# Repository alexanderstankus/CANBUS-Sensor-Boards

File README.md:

# CANBUS-Sensor-Boards
Schematic + Layout for CANBUS Protocol, IMU, Wheel Speed, and Suspension following FSAE regulation
# Overview
Prototype node boards for CAN Bus communication featuring an IMU, Wheel Speed sensors, and Suspension sensors. 
# Features
* STM32 (MCU)
* CAN Transceiver MCP2551
* Multiple Buck Converters per board (24v to 5v) and (5v to 3.3v)
# Technical Specifications
* 2 Layer Boards
* 24v Max Input

# Schematic and Layout Examples

Schematic for IMU + STM32

Layout for IMU + STM32

#
The other 2 Schematics and Layouts (wheel speed sensor and suspension sensors) can be found in the exports folder within the repo.

Designed in KiCad by Alexander Stankus

GitHub: @alexanderstankus

Email: alexstankus99@gmail.com

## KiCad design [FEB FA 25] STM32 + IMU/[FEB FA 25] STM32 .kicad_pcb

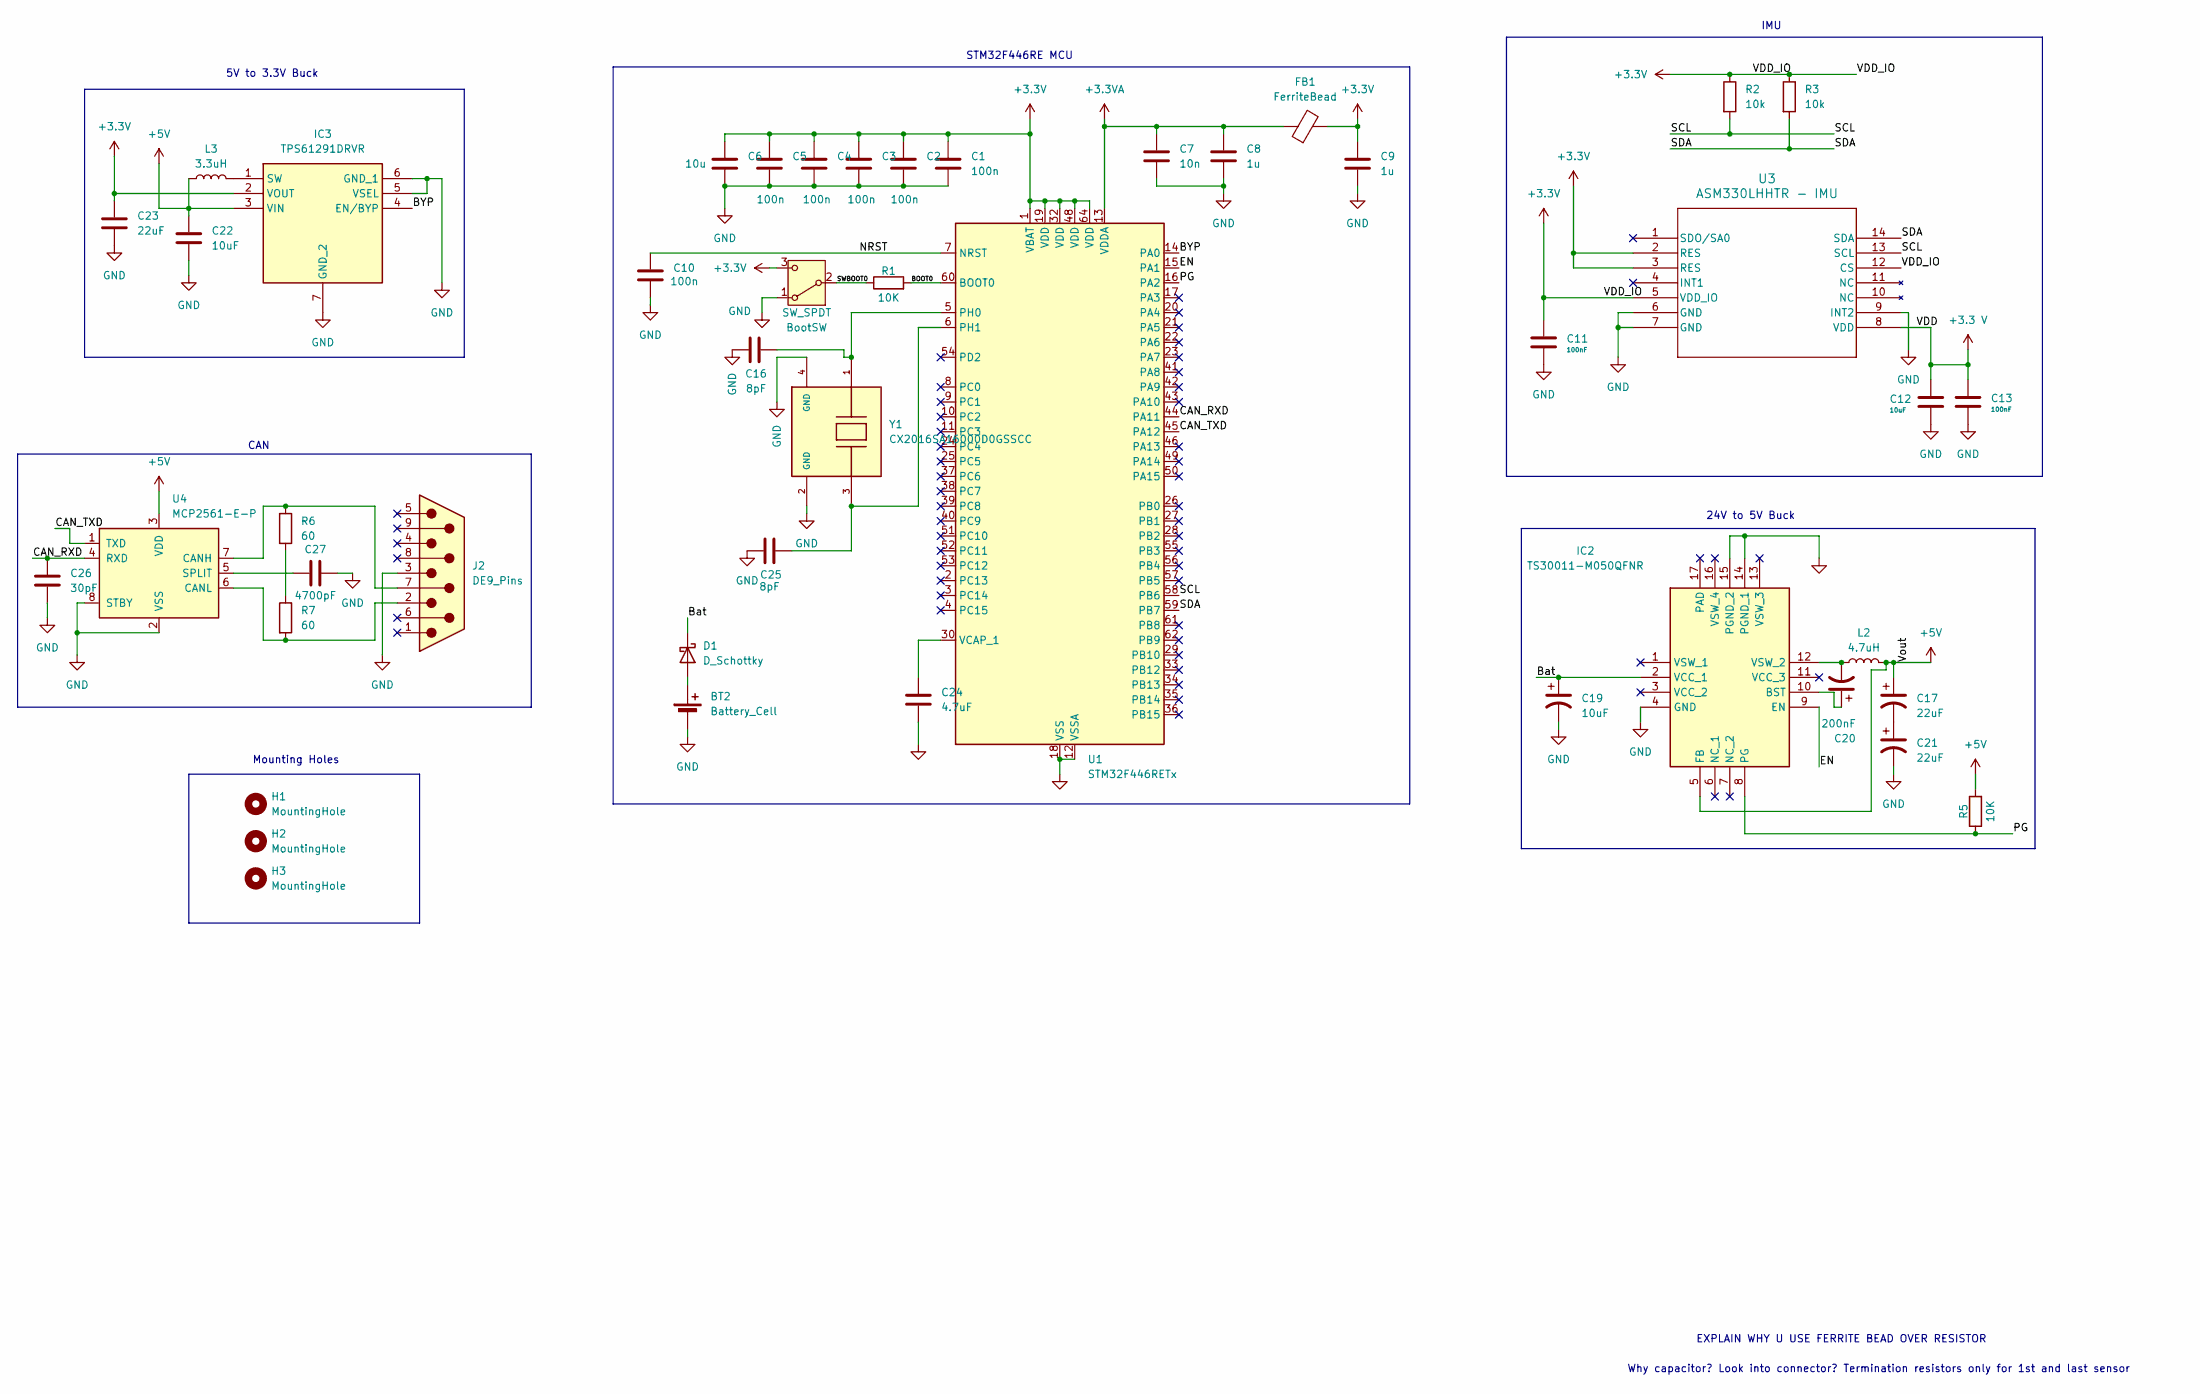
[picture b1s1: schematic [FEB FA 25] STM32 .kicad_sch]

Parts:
BT2: Battery_Cell; 691137710002
BootSW: SW_SPDT; SW_SPDT_CK_JS102011SAQN
C1, C2, C3, C4, C5, C10: 100n; C_0201_0603Metric
C6: 10u; C_1206_3216Metric
C7: 10n; C_0201_0603Metric
C8, C9: 1u; C_0201_0603Metric
C11, C13: 100nF; C_0201_0603Metric
C12, C19, C22: 10uF; C_1206_3216Metric
C16, C25: 8pF; C_0201_0603Metric
C17, C21, C23: 22uF; C_0603_1608Metric
C20: 200nF; C_0603_1608Metric
C24: 4.7uF; C_0201_0603Metric
C26: 30pF; C_0402_1005Metric
C27: 4700pF; C_0603_1608Metric
D1: D_Schottky; D_SMC
FB1: FerriteBead; Crystal_SMD_0603-4Pin_6.0x3.5mm
H1, H2, H3: MountingHole; MountingHole_2.2mm_M2
IC2: TS30011-M050QFNR; Mouser Part Number 947-TS30011-M050QFNR
IC3: TPS61291DRVR; Mouser Part Number 595-TPS61291DRVR
J2: DE9_Pins; DSUB-9_Pins_EdgeMount_P2.77mm
L2: 4.7uH; L_0603_1608Metric
L3: 3.3uH; L_1210_3225Metric
R1, R5: 10K; R_0201_0603Metric
R2, R3: 10k; R_0201_0603Metric
R6, R7: 60; R_1206_3216Metric
U1: STM32F446RETx; LQFP-64_10x10mm_P0.5mm
U3: ASM330LHHTR - IMU
U4: MCP2561-E-P; DIP-8_W7.62mm
Y1: CX2016SA16000D0GSSCC; OSCCC200X160X50N

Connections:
+3.3 V: C12.1, C13.2, U3.8 (VDD)
+3.3V: BootSW.3 (C), C1.1, C2.1, C3.1, C4.1, C5.1, C6.1, C9.1, C11.1, C23.1, FB1.2, IC3.2 (VOUT), R2.1, R3.1, U1.1 (VBAT), U1.19 (VDD), U1.32 (VDD), U1.48 (VDD), U1.64 (VDD), U3.2 (RES), U3.3 (RES), U3.5 (VDD_IO), U3.12 (CS); also elsewhere on the board
+3.3VA: C7.1, C8.1, FB1.1, U1.13 (VDDA)
+5V: C17.1, C22.1, IC2.5 (FB), IC3.3 (VIN), L2.2, L3.1, R5.2, U4.3 (VDD)
/BOOT0: R1.2, U1.60 (BOOT0)
/BYP: IC3.4 (EN/BYP), U1.14 (PA0)
/Bat: C19.1, D1.1 (K), IC2.2 (VCC_1)
/CAN_RXD: C26.2, U1.44 (PA11), U4.4 (RXD)
/CAN_TXD: U1.45 (PA12), U4.1 (TXD)
/EN: IC2.9 (EN), U1.15 (PA1)
/NRST: C10.1, U1.7 (NRST)
/PG: IC2.8 (PG), R5.1, U1.16 (PA2)
/SCL: R2.2, U1.58 (PB6), U3.13 (SCL)
/SDA: R3.2, U1.59 (PB7), U3.14 (SDA)
/SWBOOT0: BootSW.2 (B), R1.1; also elsewhere on the board
GND: BT2.2 (-), BootSW.1 (A), C1.2, C2.2, C3.2, C4.2, C5.2, C6.2, C7.2, C8.2, C9.2, C10.2, C11.2, C12.2, C13.1, C16.1, C19.2, C21.2, C22.2, C23.2, C24.2, C25.1, C26.1, C27.1, IC2.4 (GND), IC2.14 (PGND_1), IC2.15 (PGND_2), IC3.5 (VSEL), IC3.6 (GND_1), IC3.7 (GND_2), J2.3, U1.12 (VSSA), U1.18 (VSS), U1.31 (VSS), U1.47 (VSS), U1.63 (VSS), U3.6 (GND), U3.7 (GND), U3.9 (INT2), U4.2 (VSS), U4.8 (STBY), Y1.2 (GND), Y1.4 (GND); also elsewhere on the board
unnamed: BT2.1 (+), D1.2 (A)
unnamed: C17.2, C21.1
unnamed: C20.1, IC2.10 (BST)
unnamed: C20.2, IC2.12 (VSW_2), L2.1
unnamed: IC3.1 (SW), L3.2
unnamed: R6.2, R7.1
unnamed: C16.2, U1.5 (PH0), Y1.1
unnamed: C25.2, U1.6 (PH1), Y1.3
unnamed: C24.1, U1.30 (VCAP_1)
unnamed: J2.7, R6.1, U4.7 (CANH)
unnamed: J2.2, R7.2, U4.6 (CANL)
unnamed: C27.2, U4.5 (SPLIT)

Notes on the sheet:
EXPLAIN WHY U USE FERRITE BEAD OVER RESISTOR
Why capacitor? Look into connector? Termination resistors only for 1st and last sensor
Mounting Holes
CAN
STM32F446RE MCU
24V to 5V Buck
IMU
5V to 3.3V Buck

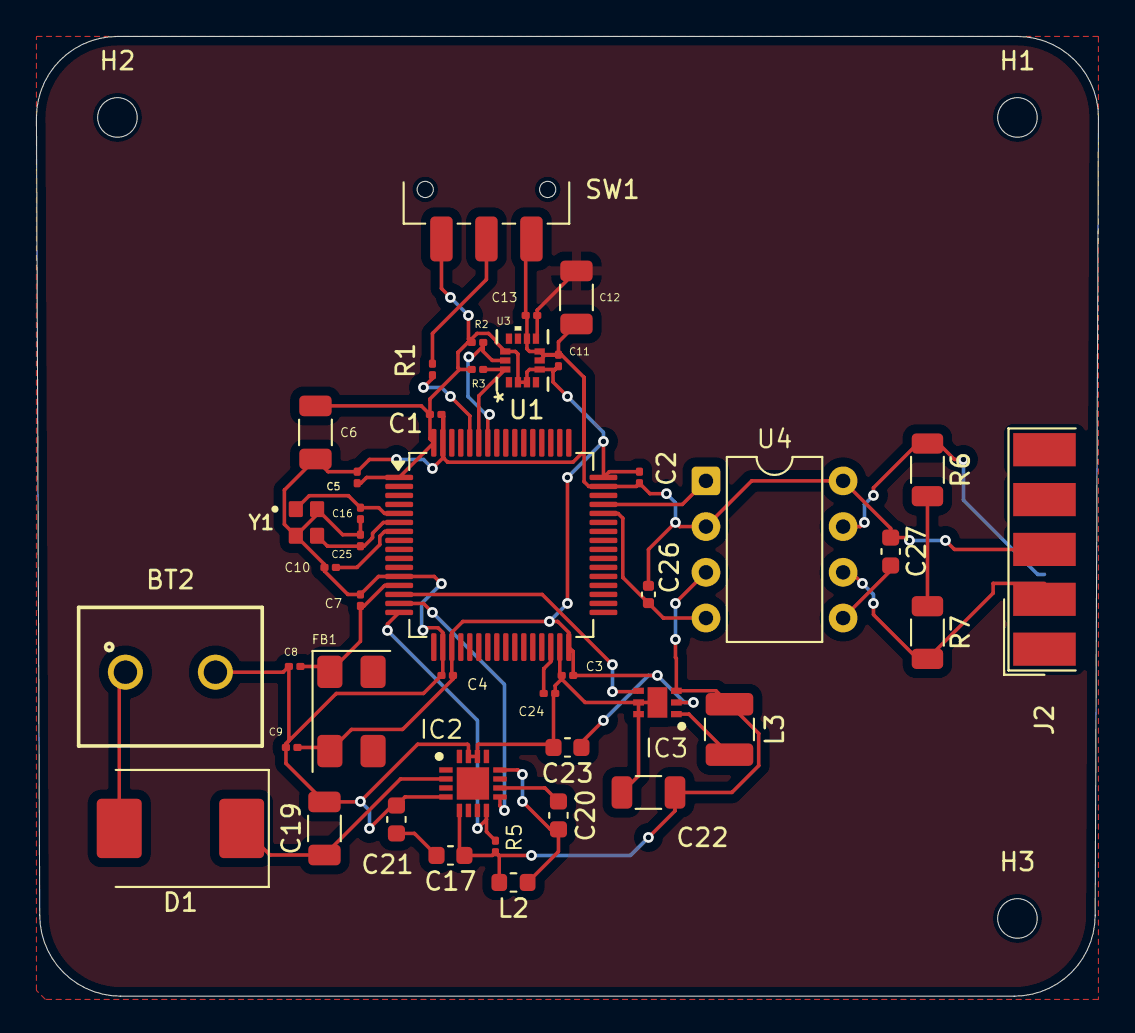
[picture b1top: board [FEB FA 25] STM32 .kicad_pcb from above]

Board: 2 copper layers, 59.0 x 53.3 mm, 46 parts (0 on the bottom side), 28 nets.

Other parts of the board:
SW1: BootSW; SW_SPDT_CK_JS102011SAQN

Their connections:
+3.3V: SW1.3 (C); also elsewhere on the board
/SWBOOT0: SW1.2 (B); also elsewhere on the board
GND: SW1.1 (A); also elsewhere on the board

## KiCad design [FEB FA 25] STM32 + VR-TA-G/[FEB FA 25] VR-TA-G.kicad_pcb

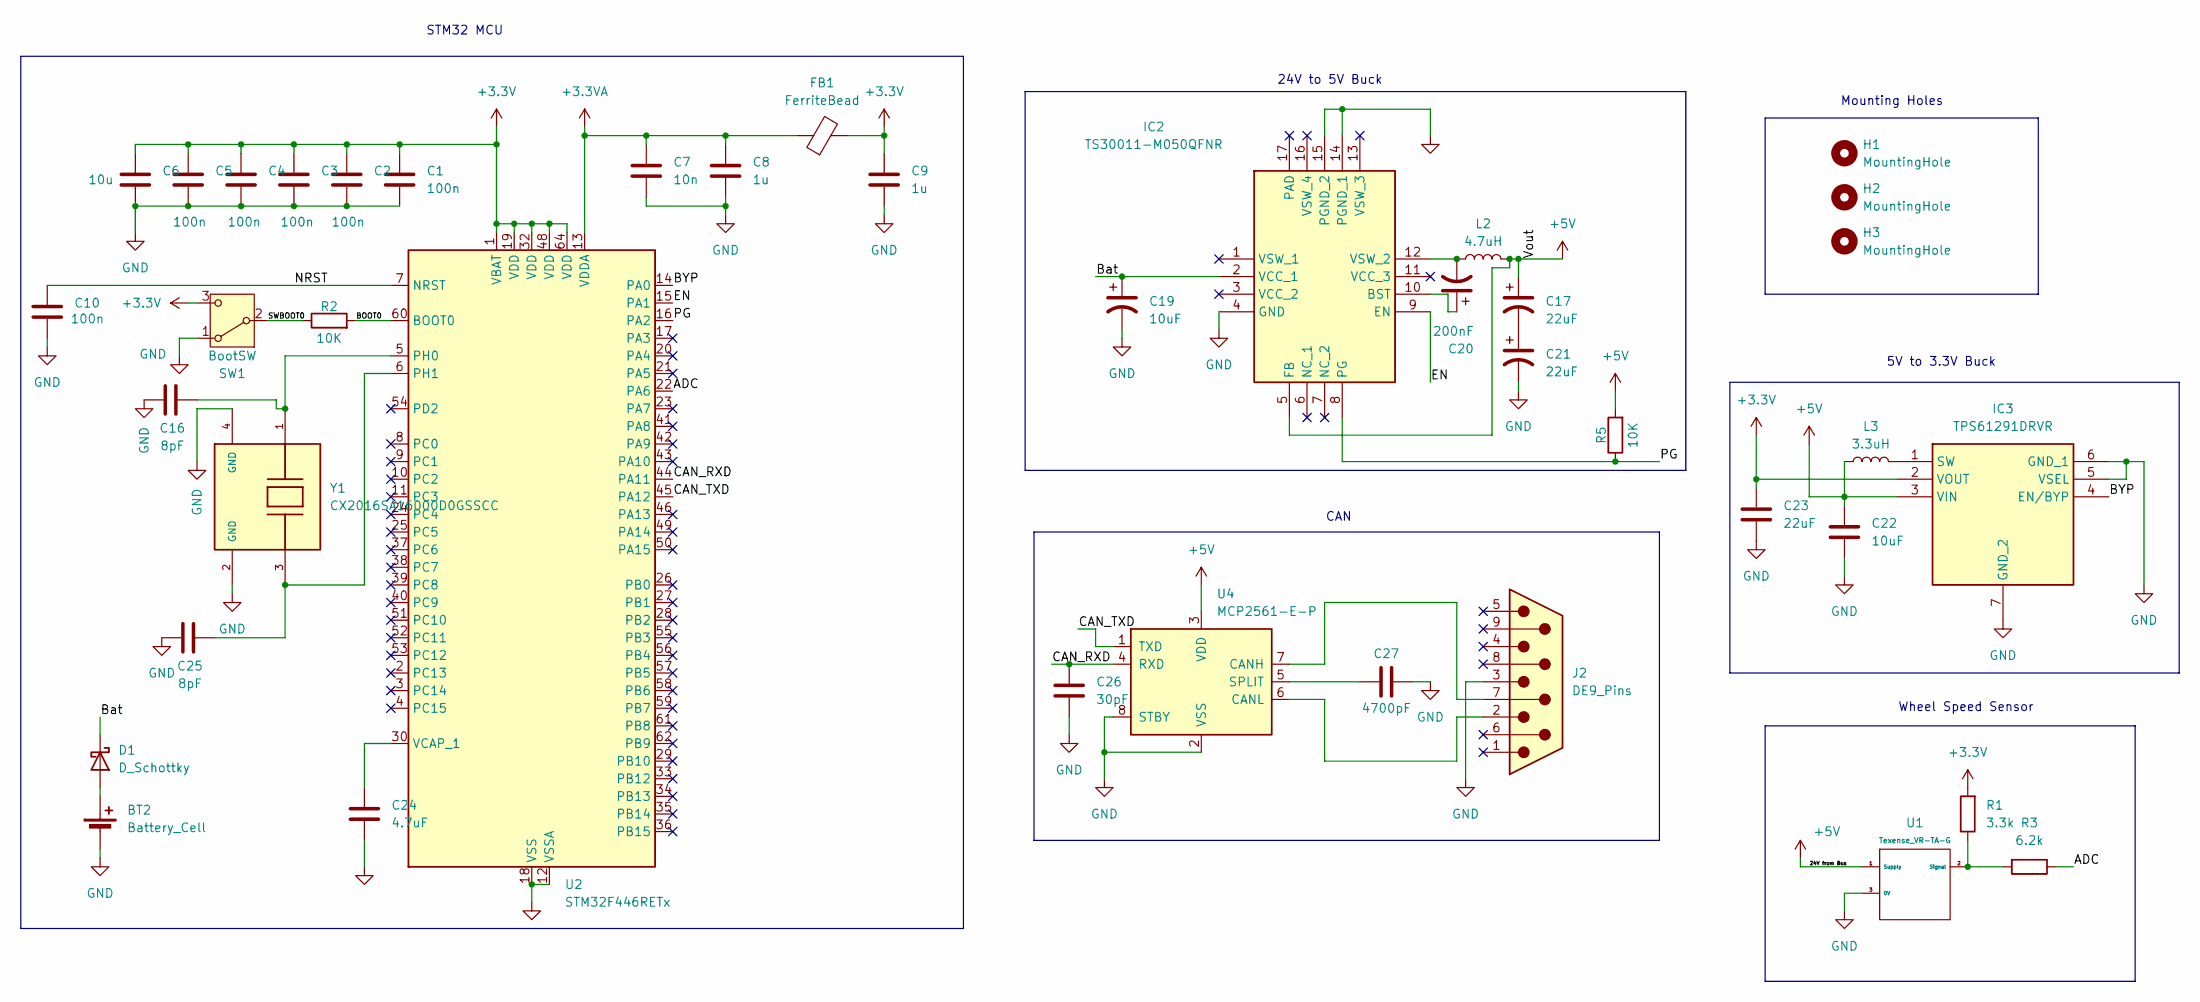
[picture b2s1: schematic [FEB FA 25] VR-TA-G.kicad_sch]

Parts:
BT2: Battery_Cell; 691137710002
C1, C2, C3, C4, C5, C10: 100n; C_0201_0603Metric
C6: 10u; C_1206_3216Metric
C7: 10n; C_0201_0603Metric
C8, C9: 1u; C_0201_0603Metric
C16, C25: 8pF; C_0201_0603Metric
C17, C21, C23: 22uF; C_0603_1608Metric
C19, C22: 10uF; C_1206_3216Metric
C20: 200nF; C_0603_1608Metric
C24: 4.7uF; C_0201_0603Metric
C26: 30pF; C_0402_1005Metric
C27: 4700pF; C_0603_1608Metric
D1: D_Schottky; D_SMC
FB1: FerriteBead; Crystal_SMD_0603-4Pin_6.0x3.5mm
H1, H2, H3: MountingHole; MountingHole_2.2mm_M2
IC2: TS30011-M050QFNR; Mouser Part Number 947-TS30011-M050QFNR
IC3: TPS61291DRVR; Mouser Part Number 595-TPS61291DRVR
J2: DE9_Pins; DSUB-9_Pins_EdgeMount_P2.77mm
L2: 4.7uH; L_0603_1608Metric
L3: 3.3uH; L_1210_3225Metric
R1: 3.3k; R_0201_0603Metric
R2, R5: 10K; R_0201_0603Metric
R3: 6.2k; R_0201_0603Metric
SW1: BootSW; SW_SPDT_CK_JS102011SAQN
U1: Texense_VR-TA-G; CONN_1988817
U2: STM32F446RETx; LQFP-64_10x10mm_P0.5mm
U4: MCP2561-E-P; DIP-8_W7.62mm
Y1: CX2016SA16000D0GSSCC; OSCCC200X160X50N

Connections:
+3.3V: C1.1, C2.1, C3.1, C4.1, C5.1, C6.1, C9.1, C23.1, FB1.2, IC3.2 (VOUT), R1.2, SW1.3 (C), U2.1 (VBAT), U2.19 (VDD), U2.32 (VDD), U2.48 (VDD), U2.64 (VDD)
+3.3VA: C7.1, C8.1, FB1.1, U2.13 (VDDA)
+5V: C17.1, C22.1, IC2.5 (FB), IC3.3 (VIN), L2.2, L3.1, R5.2, U1.1 (Supply), U4.3 (VDD)
/ADC: R3.1, U2.22 (PA6)
/BOOT0: R2.2, U2.60 (BOOT0)
/BYP: IC3.4 (EN/BYP), U2.14 (PA0)
/Bat: C19.1, D1.1 (K), IC2.2 (VCC_1)
/CAN_RXD: C26.2, U2.44 (PA11), U4.4 (RXD)
/CAN_TXD: U2.45 (PA12), U4.1 (TXD)
/EN: IC2.9 (EN), U2.15 (PA1)
/NRST: C10.1, U2.7 (NRST)
/PG: IC2.8 (PG), R5.1, U2.16 (PA2)
/SWBOOT0: R2.1, SW1.2 (B)
GND: BT2.2 (-), C1.2, C2.2, C3.2, C4.2, C5.2, C6.2, C7.2, C8.2, C9.2, C10.2, C16.1, C19.2, C21.2, C22.2, C23.2, C24.2, C25.1, C26.1, C27.1, IC2.4 (GND), IC2.14 (PGND_1), IC2.15 (PGND_2), IC3.5 (VSEL), IC3.6 (GND_1), IC3.7 (GND_2), J2.3, SW1.1 (A), U1.3 (0V), U2.12 (VSSA), U2.18 (VSS), U2.31 (VSS), U2.47 (VSS), U2.63 (VSS), U4.2 (VSS), U4.8 (STBY), Y1.2 (GND), Y1.4 (GND)
unnamed: BT2.1 (+), D1.2 (A)
unnamed: C17.2, C21.1
unnamed: C20.1, IC2.10 (BST)
unnamed: C20.2, IC2.12 (VSW_2), L2.1
unnamed: IC3.1 (SW), L3.2
unnamed: R1.1, R3.2, U1.2 (Signal)
unnamed: C16.2, U2.5 (PH0), Y1.1
unnamed: C25.2, U2.6 (PH1), Y1.3
unnamed: C24.1, U2.30 (VCAP_1)
unnamed: J2.7, U4.7 (CANH)
unnamed: J2.2, U4.6 (CANL)
unnamed: C27.2, U4.5 (SPLIT)

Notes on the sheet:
24V to 5V Buck
5V to 3.3V Buck
Mounting Holes
STM32 MCU
Wheel Speed Sensor
CAN

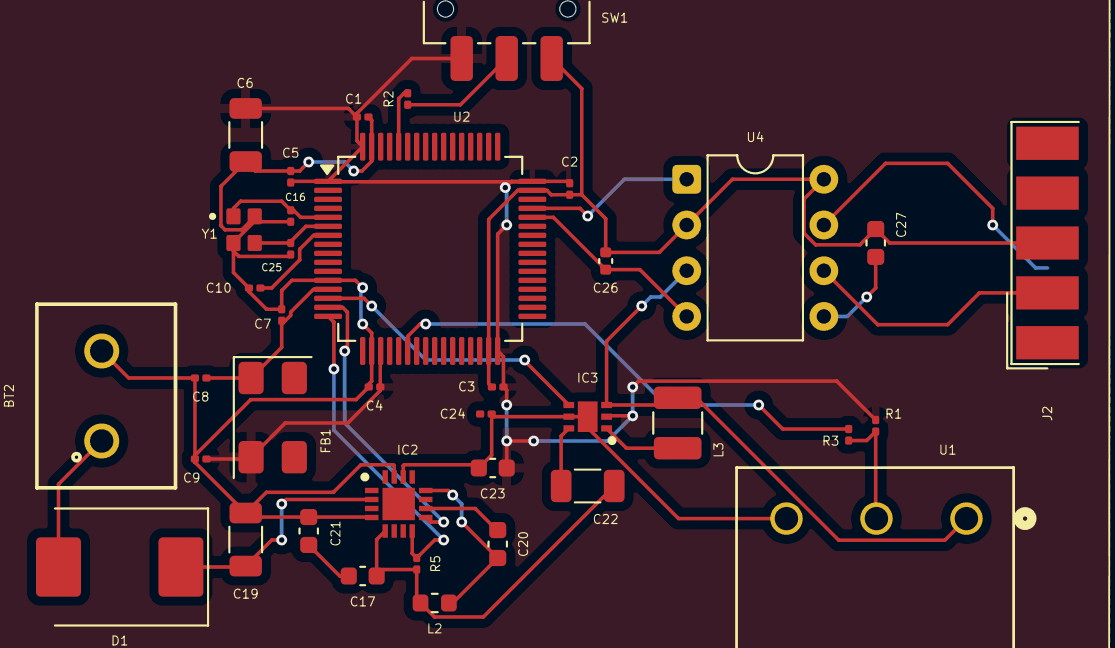
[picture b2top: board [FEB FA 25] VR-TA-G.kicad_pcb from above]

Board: 2 copper layers, 41 parts (0 on the bottom side), 26 nets.

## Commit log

2025-12-21 Init commit: Added CANBUS KiCad files
2026-01-04 Add exports to folder with sch and pcb
